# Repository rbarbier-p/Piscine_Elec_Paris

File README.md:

## BOM

| Manufacture Part Number | Manufacturer               | Package      | Description                      | Quantity |
| ----------------------- | -------------------------- | ------------ | -------------------------------- | -------- |
| ATMEGA328P-AU           | MICROCHIP                  | TQFP-32(7x7) | AVR Microcontroller - ATmega328p | 1        |
| X322516MLB4SI           | YXC Crystal Oscillators    | SMD3225-4P   | Crystal Oscillator - 16MHz 9pF   | 1        |
| B3U-1000P               | OMRON                      | SMD,3x2.5mm  | Round Button - 2.5mm 12V         | 1        |
| TZ-P2-0603YGTCS1-0.6T   | TUOZHAN                    | 0603         | Indication LED - Green 1.9V~2.4V | 1        |
| XL-1608SURC-06          | XINGLIGHT                  | 0603         | Indication LED - Red 2.3V        | 1        |
| CL10A105KB8NNNC         | Samsung Electro-Mechanics  | 0603         | Ceramic Capacitor - 1uF 50V      | 1        |
| CC0603KRX7R9BB104       | YAGEO                      | 0603         | Ceramic Capacitor - 100nF 50V    | 3        |
| CL10C120JB8NNNC         | Samsung Electro-Mechanics  | 0603         | Ceramic Capacitor - 12pF 50V     | 2        |
| RC0603FR-0710KL         | YAGEO                      | 0603         | Chip Resistor - 10kΩ 75V         | 2        |
| 0603WAF3300T5E          | UNI-ROYAL                  | 0603         | Chip Resistor - 330Ω 75V         | 1        |

<br>

## Pinout Description

<pre>
      _⎽⎽⎽⎽⎽⎽⎽⎽⎽_⎽_⎽_
   30|○                  ○|1
   29|○                  ○|2
   28|○                  ○|3
   27|○                  ○|4
   26|○                  ○|5
   25|○                  ○|6
   24|○                  ○|7
   23|○                  ○|8
   22|○                  ○|9
   21|○                  ○|10
   20|○                  ○|11
   19|○ ◻  ○  ○  ○  ○  ○ ○|12
      ⎺⎺⎺⎺⎺⎺⎺⎺⎺⎺⎺⎺⎺
       18 17 16 15 14 13
  
</pre>

| Board Pin | Pin type | ATmega328p Pin |
| :-: | :-: | :-: |
| 1 | D9 | PB1 | D4 / PD4 | D3 / PD3 | D2 / PD2 | GND | RST  | RXI  | TXO |
| 2 | D8 | PB0 | | GND | RST | VCC | A3  | A2  | A1  | A0  | SCK | MISO | MOSI | D10 |
| 3 | D7 | PD7 | | RXI | VCC | GND | GND |     |     |     |      |      |     |
| 4 | D6 | PD6 |
| 5 | D5 | PD5 |
| 6 | D4 | PD4 |
| 7 | D3 | PD3 |
| 8 | D2 | PD2 |
| 9 | GND | - |
| 10 | RST | R̅E̅S̅E̅T̅/PC6
| 11 | RXI | PD0
| 12 | TXO | PD1
| 13 | GND | -
| 14 | GND | -
| 15 | VCC | -
| 16 | RXI | PD0
| 17 | TXO | PD1
| 18 | DTR | R̅E̅S̅E̅T̅/PC6
| 19 | RAW | -
| 20 | GND | -
| 21 | RST | R̅E̅S̅E̅T̅/PC6
| 22 | VCC | - 
| 23 | A3 | PC3
| 24 | A2 | PC2
| 25 | A1 | PC1
| 26 | A0 | PC0
| 27 | SCK | PB5
| 28 | MISO | PB4
| 29 | MOSI |PB3
| 30 | D10 | PB2

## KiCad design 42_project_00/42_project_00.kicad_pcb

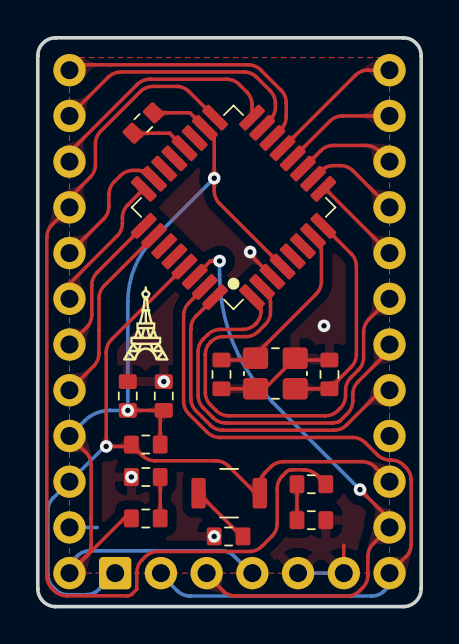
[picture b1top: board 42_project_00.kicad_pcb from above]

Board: 2 copper layers, 21.3 x 31.6 mm, 17 parts (0 on the bottom side), 27 nets.

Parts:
C1, C2, C5: 12pF; 0603_CA_C
C4, C7: 100nF; 0603_CA_C
C6: 1uF; 0603_CA_C
D1: Green; 0603_CA_D
D2: Red; 0603_CA_D
J1, J2: SidePorts
J3: FTDI
R1: 330; 0603_CA_R
R2, R3: 10k; 0603_CA_R
SW1: SW_Push; Omron_B3U-1000P
U1: ATmega328p-A; ATmega328p-AU
Y1: 16Mhz; Crystal

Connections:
A0: J2.26, U1.23 (PC0)
A1: J2.25, U1.24 (PC1)
A2: J2.24, U1.25 (PC2)
A3: J2.23, U1.26 (PC3)
D2: J1.8, U1.32 (PD2)
D3: J1.7, U1.1 (PD3)
D4: J1.6, U1.2 (PD4)
D5: J1.5, U1.9 (PD5)
D6: J1.4, U1.10 (PD6)
D7: J1.3, U1.11 (PD7)
D8: J1.2, U1.12 (PB0)
D9: J1.1, U1.13 (PB1)
D10: J2.30, U1.14 (PB2)
DTR: J1.10, J2.21, J3.18, R3.1, SW1.2, U1.29 (RESET/PC6)
GND: C1.2, C2.2, C4.1, C6.2, C7.2, D1.2, J1.9, J2.20, J3.13, J3.14, R2.1, U1.3 (GND), Y1.2, Y1.4
MISO: J2.28, U1.16 (PB4)
MOSI: J2.29, U1.15 (PB3)
unnamed: C4.2, SW1.1
unnamed: D1.1, R1.1
unnamed: D2.2, R2.2
unnamed: C5.2, U1.20 (AREF)
unnamed: C1.1, U1.8 (XTAL2/PB7), Y1.3
unnamed: C2.1, U1.7 (XTAL/PB6), Y1.1
RAW: C5.1, C6.1, C7.1, D2.1, J2.19, J2.22, J3.15, R3.2, U1.4 (VCC), U1.18 (AVCC)
RXI: J1.11, J3.16, U1.30 (PD0)
SCK: J2.27, R1.2, U1.17 (PB5)
TXO: J1.12, J3.17, U1.31 (PD1)

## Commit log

2025-11-18 test
2025-11-18 working docker
2025-11-19 hoola
2025-11-20 mandatory done, check RAW
2025-11-21 bonus done, diferential pairs ?
2025-11-21 new names, kicad_sch warning?
2025-11-22 pdfs
2025-11-22 Add pinout and BOM details to README
    Added pinout and BOM information to the README.
2025-11-22 Fix formatting of LED description in README.md
2025-11-22 merged pdfs
2025-11-24 better readme
    Updated the BOM and pinout sections with improved formatting and additional details.
